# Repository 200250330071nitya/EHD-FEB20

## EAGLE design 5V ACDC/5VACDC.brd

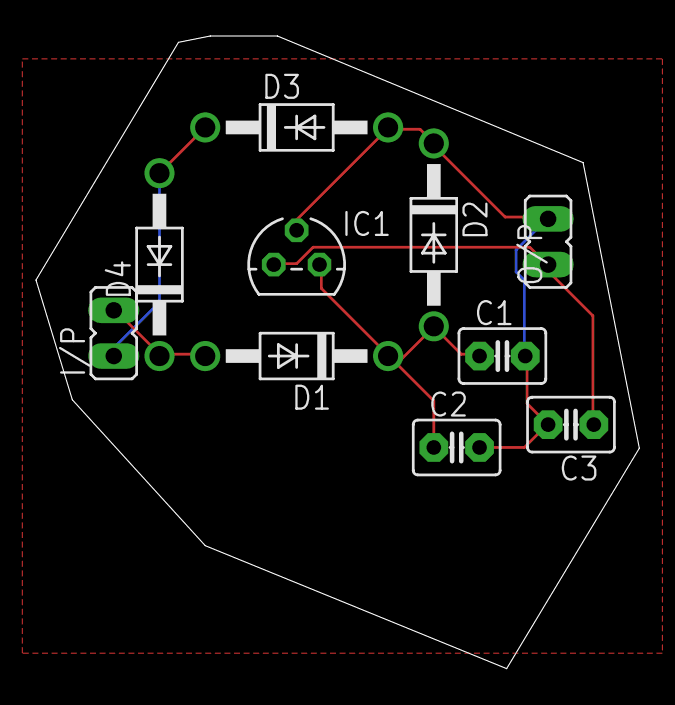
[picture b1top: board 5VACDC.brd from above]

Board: 2 copper layers, 33.5 x 35.1 mm, 10 parts (0 on the bottom side), 5 nets.

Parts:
C1, C3: C2.5-3
C2: 0.5; C2.5-3
D1, D2, D3, D4: 1N4004; DO41-10
I/P: JP1
IC1: 7805L; TO92
O/P: JP1

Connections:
unnamed: D1.A, D4.C, I/P.2
unnamed: C1.1, C2.1, D1.C, D2.A, IC1.3
unnamed: C1.2, C2.2, C3.2, D2.C, D3.A, IC1.2, O/P.2
unnamed: D3.C, D4.A, I/P.1
unnamed: C3.1, IC1.1, O/P.1
